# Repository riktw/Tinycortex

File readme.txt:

A tiny MBED compatible board. 
In here are all the hardware design files and an GCC compatible blink a led.
Pinout and other helpfull files can be found here too. For more information have a look at the following blog posts:

http://justanotherelectronicsblog.com/?p=124
http://justanotherelectronicsblog.com/?p=139

Everything is cc-by-sa-3.0 licensed unless said otherwise

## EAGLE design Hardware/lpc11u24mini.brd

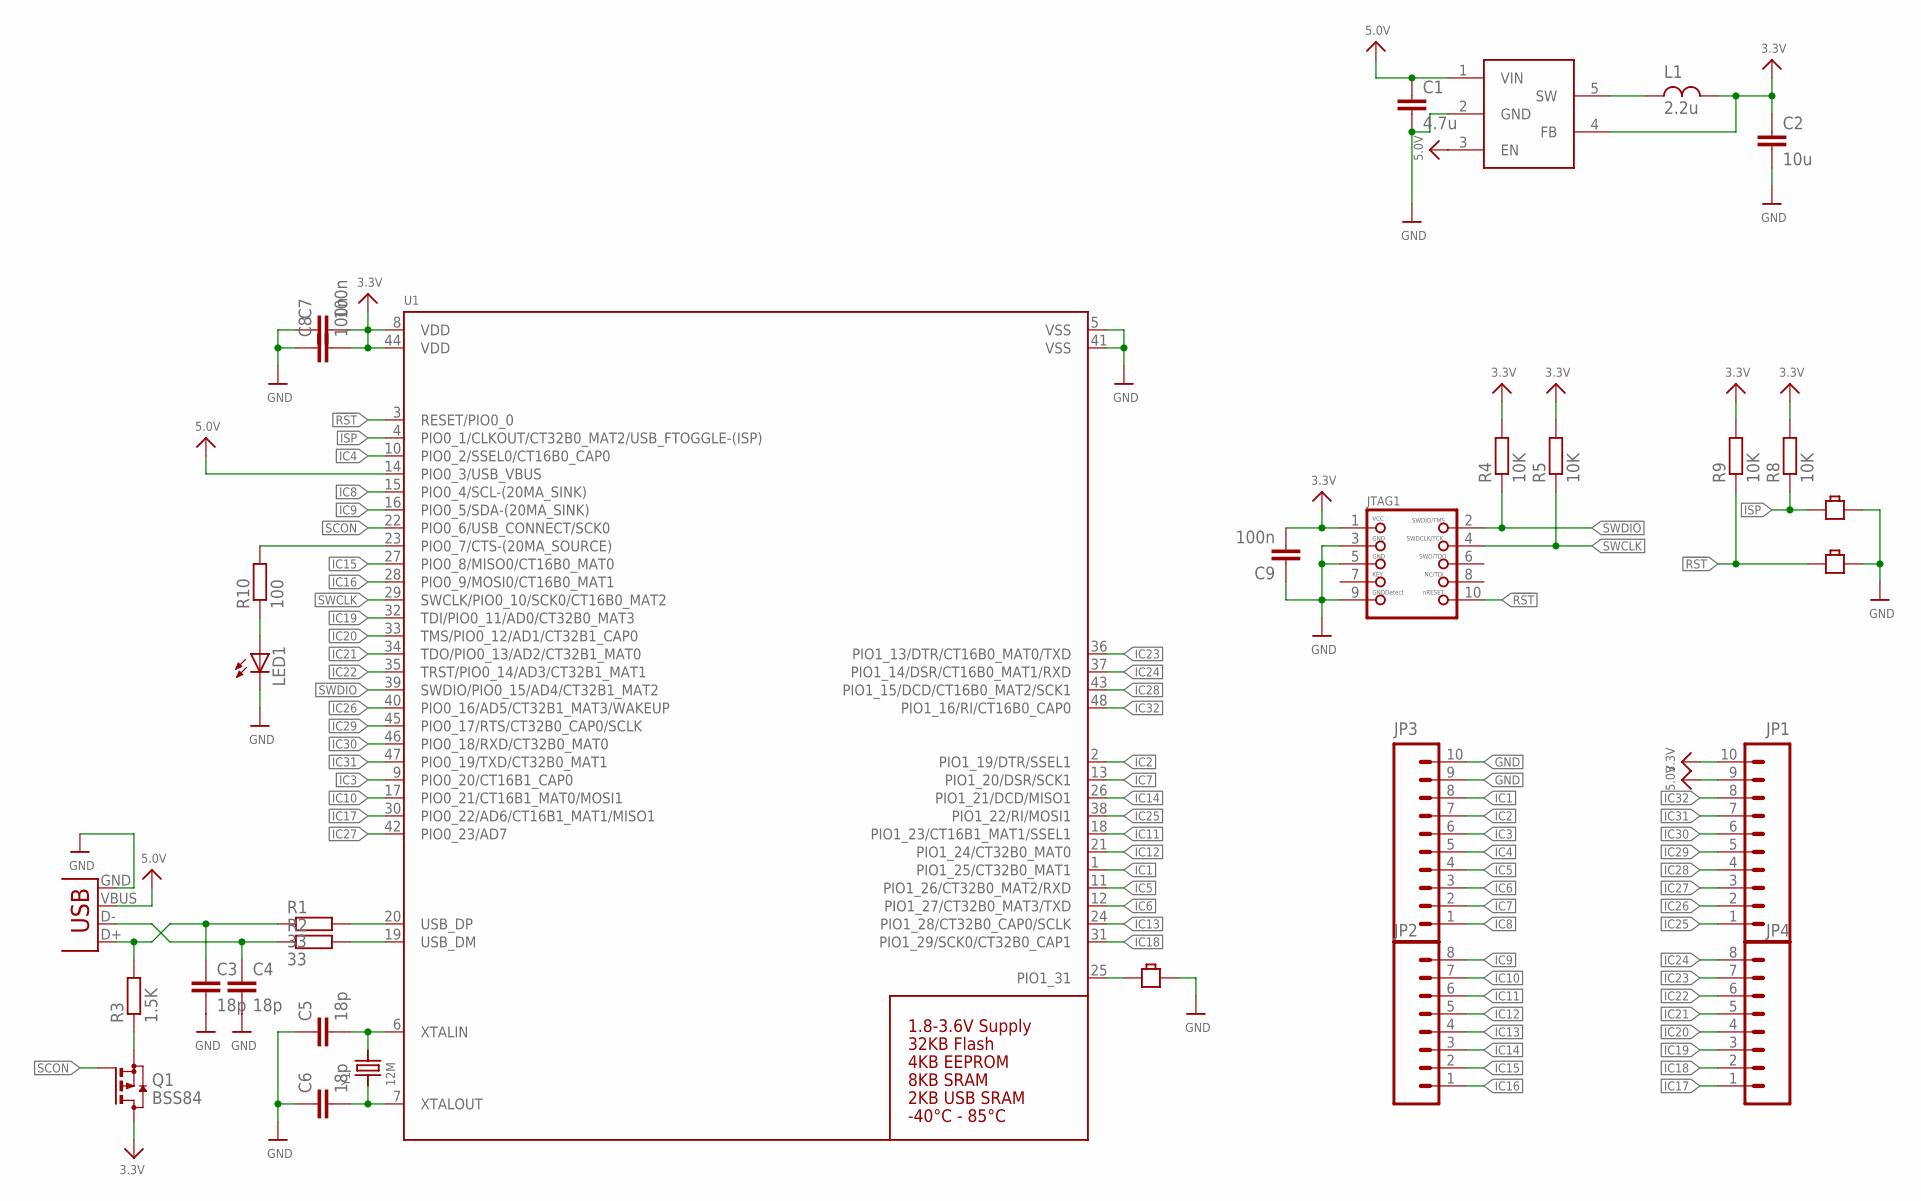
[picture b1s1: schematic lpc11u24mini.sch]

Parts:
B1, B2, B3: BUTTON-SMD-2P; BUTTON_2P_SMD
C1: 4.7u; C0603
C2: 10u; C0603
C3, C4, C5, C6: 18p; C0603
C7, C8, C9: 100n; C0603
JP1, JP3: M10SMD_MALE; 1X10_SMD_MALE
JP2, JP4: M08SMD-MALE; 1X08_SMD_MALE
JTAG1: JTAG-CORTEXM3; 2X05_1.27MM_SMT
L1: 2.2u; SRN2512
LED1: LEDSML0805; SML0805
Q1: BSS84; SOT23
R1, R2: 33; R0603
R3: 1.5K; R0603
R4, R5, R8, R9: 10K; R0603
R10: 100; R0603
U1: LPC11U24_QFP48; LQFP48
U$3: LM3671; SOT23-5
X1: USB-MICROB
Y1: 12M; CRYSTAL_3.2X2.5

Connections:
3.3V: C2.1, C7.2, C8.2, C9.2, JP1.10, JTAG1.1, L1.P$2 (2), Q1.3 (D), R4.2, R5.2, R8.2, R9.2, U1.8 (VDD), U1.44 (VDD), U$3.4 (FB)
5.0V: C1.1, JP1.9, U1.14 (PIO0_3/USB_VBUS), U$3.1 (VIN), U$3.3 (EN), X1.VBUS
!RST: B2.1, JTAG1.10, R9.1, U1.3 (RESET/PIO0_0)
DR_N: R2.2, U1.19 (USB_DM)
DR_P: R1.2, U1.20 (USB_DP)
D_N: C4.1, R2.1, X1.D-
D_P: C3.1, R1.1, R3.2, X1.D+
GND: B1.P$2, B2.P$2, B3.P$2, C1.2, C2.2, C3.2, C4.2, C5.1, C6.1, C7.1, C8.1, C9.1, JP3.9, JP3.10, JTAG1.3, JTAG1.5, JTAG1.9, LED1.C, U1.5 (VSS), U1.41 (VSS), U$3.2 (GND), X1.GND
IC1: JP3.8, U1.1 (PIO1_25/CT32B0_MAT1)
IC2: JP3.7, U1.2 (PIO1_19/DTR/SSEL1)
IC3: JP3.6, U1.9 (PIO0_20/CT16B1_CAP0)
IC4: JP3.5, U1.10 (PIO0_2/SSEL0/CT16B0_CAP0)
IC5: JP3.4, U1.11 (PIO1_26/CT32B0_MAT2/RXD)
IC6: JP3.3, U1.12 (PIO1_27/CT32B0_MAT3/TXD)
IC7: JP3.2, U1.13 (PIO1_20/DSR/SCK1)
IC8: JP3.1, U1.15 (PIO0_4/SCL-(20MA_SINK))
IC9: JP2.8, U1.16 (PIO0_5/SDA-(20MA_SINK))
IC10: JP2.7, U1.17 (PIO0_21/CT16B1_MAT0/MOSI1)
IC11: JP2.6, U1.18 (PIO1_23/CT16B1_MAT1/SSEL1)
IC12: JP2.5, U1.21 (PIO1_24/CT32B0_MAT0)
IC13: JP2.4, U1.24 (PIO1_28/CT32B0_CAP0/SCLK)
IC14: JP2.3, U1.26 (PIO1_21/DCD/MISO1)
IC15: JP2.2, U1.27 (PIO0_8/MISO0/CT16B0_MAT0)
IC16: JP2.1, U1.28 (PIO0_9/MOSI0/CT16B0_MAT1)
IC17: JP4.1, U1.30 (PIO0_22/AD6/CT16B1_MAT1/MISO1)
IC18: JP4.2, U1.31 (PIO1_29/SCK0/CT32B0_CAP1)
IC19: JP4.3, U1.32 (TDI/PIO0_11/AD0/CT32B0_MAT3)
IC20: JP4.4, U1.33 (TMS/PIO0_12/AD1/CT32B1_CAP0)
IC21: JP4.5, U1.34 (TDO/PIO0_13/AD2/CT32B1_MAT0)
IC22: JP4.6, U1.35 (TRST/PIO0_14/AD3/CT32B1_MAT1)
IC23: JP4.7, U1.36 (PIO1_13/DTR/CT16B0_MAT0/TXD)
IC24: JP4.8, U1.37 (PIO1_14/DSR/CT16B0_MAT1/RXD)
IC25: JP1.1, U1.38 (PIO1_22/RI/MOSI1)
IC26: JP1.2, U1.40 (PIO0_16/AD5/CT32B1_MAT3/WAKEUP)
IC27: JP1.3, U1.42 (PIO0_23/AD7)
IC28: JP1.4, U1.43 (PIO1_15/DCD/CT16B0_MAT2/SCK1)
IC29: JP1.5, U1.45 (PIO0_17/RTS/CT32B0_CAP0/SCLK)
IC30: JP1.6, U1.46 (PIO0_18/RXD/CT32B0_MAT0)
IC31: JP1.7, U1.47 (PIO0_19/TXD/CT32B0_MAT1)
IC32: JP1.8, U1.48 (PIO1_16/RI/CT16B0_CAP0)
ISP: B1.1, R8.1, U1.4 (PIO0_1/CLKOUT/CT32B0_MAT2/USB_FTOGGLE-(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)
LED: R10.2, U1.23 (PIO0_7/CTS-(20MA_SOURCE))
unnamed: B3.1, U1.25 (PIO1_31)
unnamed: L1.P$1 (1), U$3.5 (SW)
unnamed: Q1.2 (S), R3.1
unnamed: C6.2, U1.7 (XTALOUT), Y1.1
unnamed: C5.2, U1.6 (XTALIN), Y1.2
unnamed: LED1.A, R10.1
SCON: Q1.1 (G), U1.22 (PIO0_6/USB_CONNECT/SCK0)
SWCLK: JTAG1.4, R5.1, U1.29 (SWCLK/PIO0_10/SCK0/CT16B0_MAT2)
SWDIO: JTAG1.2, R4.1, U1.39 (SWDIO/PIO0_15/AD4/CT32B1_MAT2)

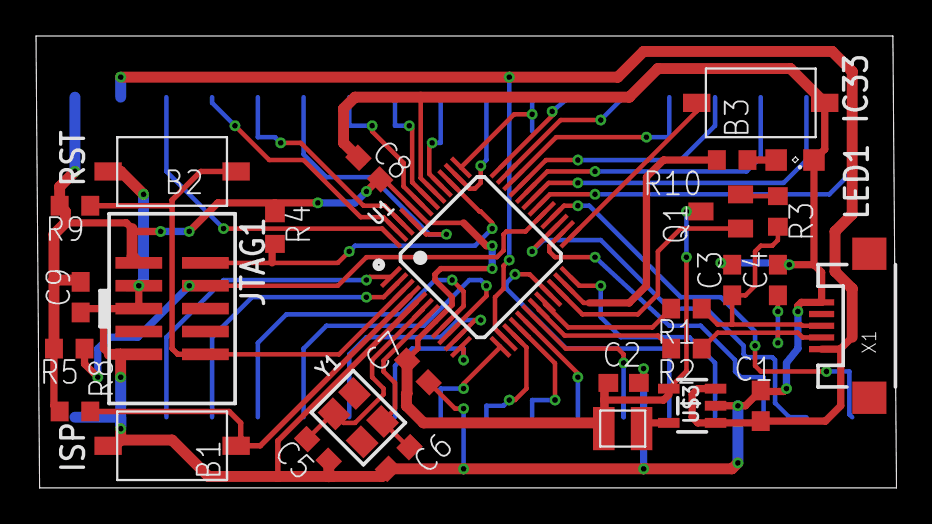
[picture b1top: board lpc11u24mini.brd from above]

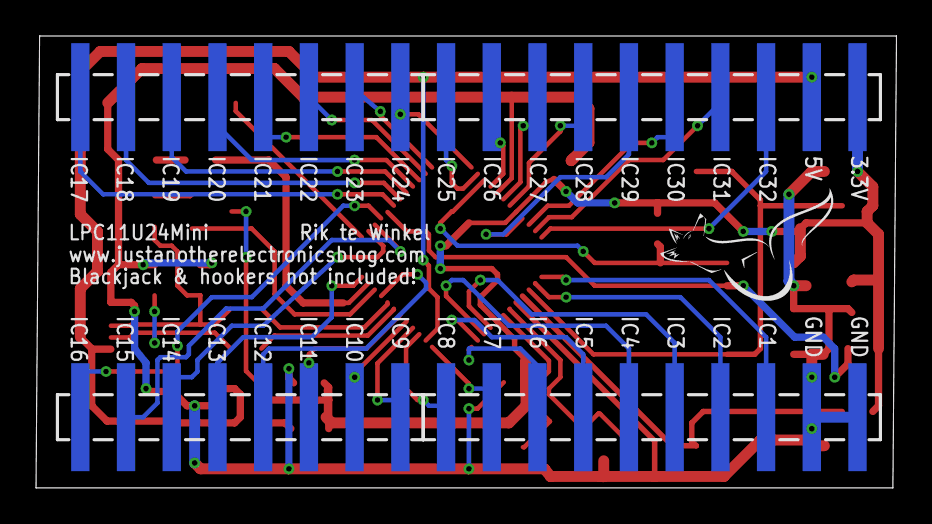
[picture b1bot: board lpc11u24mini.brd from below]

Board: 2 copper layers, 47.8 x 25.1 mm, 32 parts (4 on the bottom side), 51 nets.

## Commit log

2015-08-11 add readme.txt
2015-08-11 First real commit
2015-08-11 better pinout
2015-08-11 changed readme

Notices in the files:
parts and their libraries:
microbuilder: This work is placed in the public domain, and may be freely used for commercial and non-commercial work with the following conditions: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
SparkFun-Connectors: Licensing: Creative Commons ShareAlike 4.0 International - https://creativecommons.org/licenses/by-sa/4.0
